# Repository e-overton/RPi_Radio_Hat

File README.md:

Raspberry Pi B+ Radio Hat
============================
This board adds two AWA24S 2.4GHz DSS radio modules to the Raspberry Pi to enable remote control using radio-controller-like standards. In addition a real time clock is added to the board to keep track of time in a battery powered project.

This proect is based on the RPi template from: https://github.com/xesscorp/RPi_Hat_Template

Note this board is in development, and has not been fabricated/tested.

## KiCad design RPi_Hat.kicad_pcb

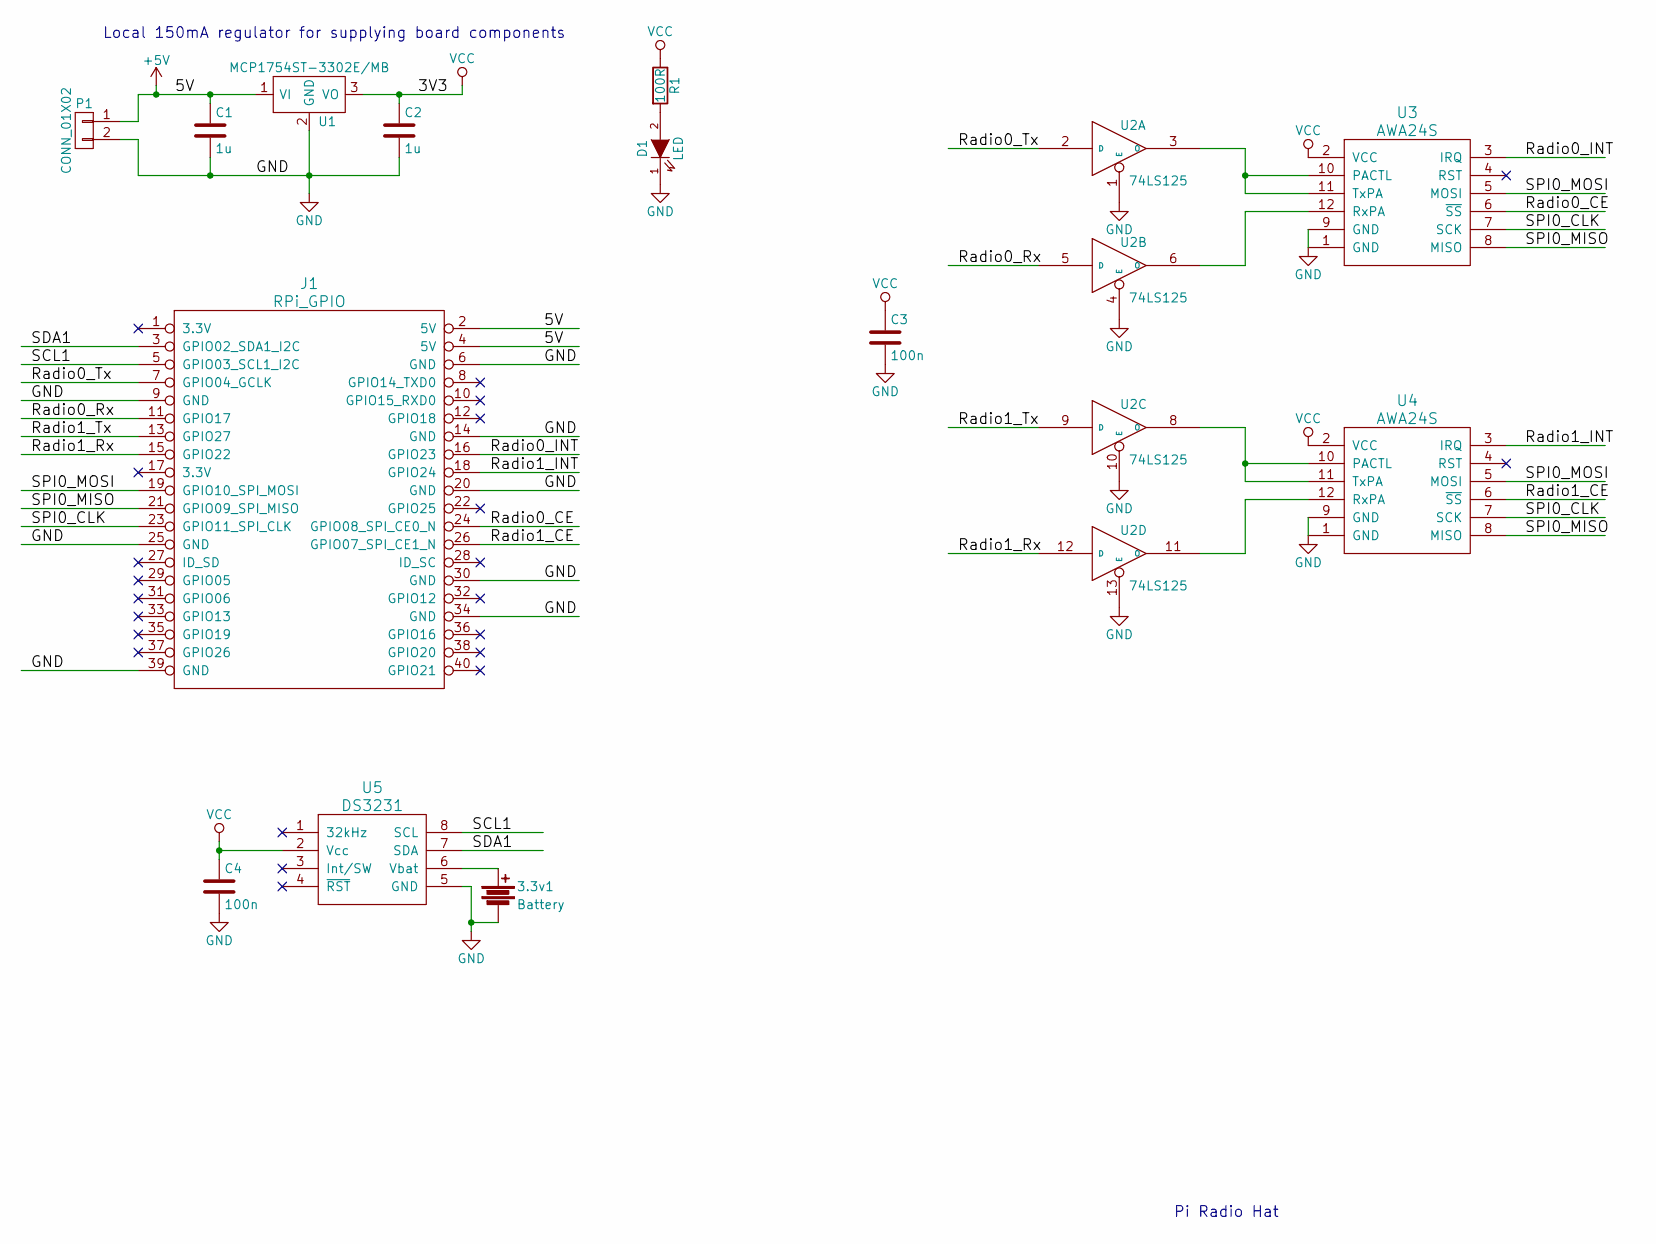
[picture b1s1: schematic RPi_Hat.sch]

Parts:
3.3v1: Battery; cr1225
C1, C2: 1u; C_1206
C3, C4: 100n; C_1206
D1: LED; LED_1206
J1: RPi_GPIO
P1: CONN_01X02; Pin_Header_Straight_1x02
R1: 100R; R_1206_HandSoldering
U1: MCP1754ST-3302E/MB; SOT-223
U2: 74LS125; SOIC-14_N
U3, U4: AWA24S
U5: DS3231; SOIC-8_3.9x4.9mm_Pitch1.27mm

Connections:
+5V: C1.1, J1.2 (5V), J1.4 (5V), P1.1, U1.1 (VI)
/Radio0_CE: J1.24 (GPIO08_SPI_CE0_N), U3.6 (~SS)
/Radio0_INT: J1.16 (GPIO23), U3.3 (IRQ)
/Radio0_Rx: J1.11 (GPIO17), U2.5 (D)
/Radio0_Tx: J1.7 (GPIO04_GCLK), U2.2 (D)
/Radio1_CE: J1.26 (GPIO07_SPI_CE1_N), U4.6 (~SS)
/Radio1_INT: J1.18 (GPIO24), U4.3 (IRQ)
/Radio1_Rx: J1.15 (GPIO22), U2.12 (D)
/Radio1_Tx: J1.13 (GPIO27), U2.9 (D)
/SCL1: J1.5 (GPIO03_SCL1_I2C), U5.8 (SCL)
/SDA1: J1.3 (GPIO02_SDA1_I2C), U5.7 (SDA)
/SPI0_CLK: J1.23 (GPIO11_SPI_CLK), U3.7 (SCK), U4.7 (SCK)
/SPI0_MISO: J1.21 (GPIO09_SPI_MISO), U3.8 (MISO), U4.8 (MISO)
/SPI0_MOSI: J1.19 (GPIO10_SPI_MOSI), U3.5 (MOSI), U4.5 (MOSI)
GND: 3.3v1.2, C1.2, C2.2, C3.2, C4.2, D1.1 (K), J1.6 (GND), J1.9 (GND), J1.14 (GND), J1.20 (GND), J1.25 (GND), J1.30 (GND), J1.34 (GND), J1.39 (GND), P1.2, U1.2 (GND), U1.4, U2.1 (E), U2.4 (E), U2.7 (GND), U2.10 (E), U2.13 (E), U3.1 (GND), U3.9 (GND), U4.1 (GND), U4.9 (GND), U5.5 (GND)
unnamed: 3.3v1.1, U5.6 (Vbat)
unnamed: D1.2 (A), R1.2
unnamed: U2.3 (O), U3.10 (PACTL), U3.11 (TxPA)
unnamed: U2.6 (O), U3.12 (RxPA)
unnamed: U2.8 (O), U4.10 (PACTL), U4.11 (TxPA)
unnamed: U2.11 (O), U4.12 (RxPA)
VCC: C2.1, C3.1, C4.1, R1.1, U1.3 (VO), U2.14 (VCC), U3.2 (VCC), U4.2 (VCC), U5.2 (Vcc)

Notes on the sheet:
Local 150mA regulator for supplying board components
Pi Radio Hat

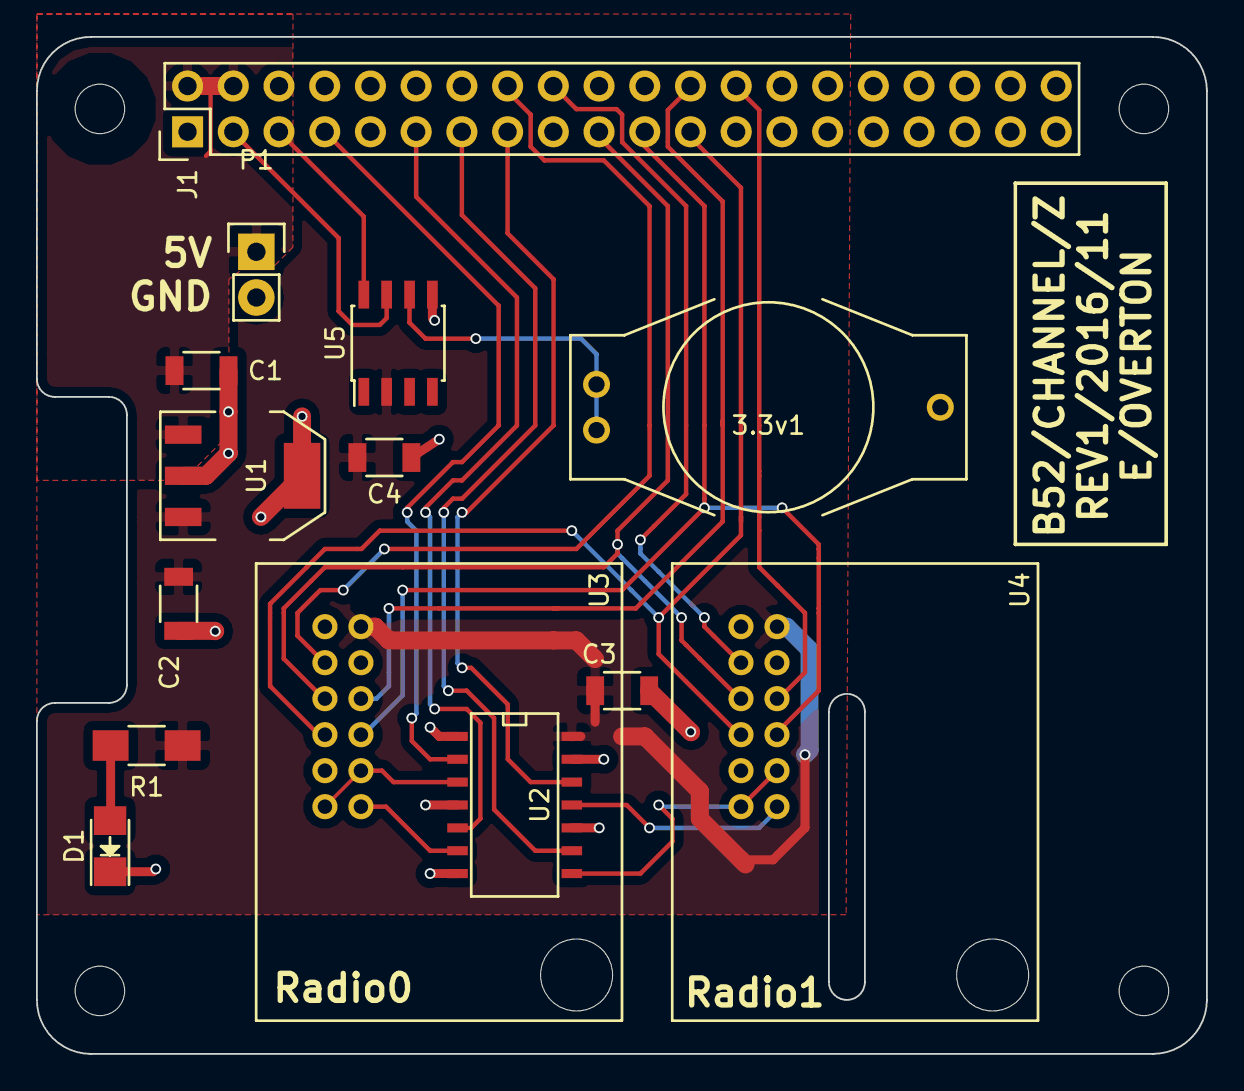
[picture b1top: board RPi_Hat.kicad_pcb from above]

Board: 2 copper layers, 65.0 x 56.5 mm, 14 parts (0 on the bottom side), 22 nets.

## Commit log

2016-11-24 Hat modified to add AWA24S radios
2016-11-30 Revised name of PCB
2016-12-02 first version to go to board house
2016-12-02 cleanup of old files, First production version
